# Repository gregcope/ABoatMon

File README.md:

ABoatMon
========

An Arduno clone based (hence the A) Boat Monitoring solution!

Intro
=====

A reimplementation, and extension of https://github.com/gregcope/piboatmon, as the original consumed too much power.  This is designed with the following goals;
* Be very, very low power and
* Monitor and charge from 12-24V

The present version is made from COTS parts to make life easy at the deign/proto stage.  However the code should be transferable.

Parts
=====
* [Adafruit Ultimate GPS](https://www.adafruit.com/product/746) - any 3.3v UART GPS would do, however needs an enable pin and vbat GPS almanac backup
* [Adafruit Fona](https://www.adafruit.com/product/1946) - any 3.3v UART GSM modem would do, although we do use the battery charging on the fona
* [Low power Atemega 1280 Moteino Mega](https://lowpowerlab.com/shop/product/119) This might fit into lower spec Atmegs, but I have no idea... The [Moteino M0 would work well](https://lowpowerlab.com/shop/product/184), although pin outs need to change.
* [Mini Step Down Regulator Voltag Power Supply Module 4.5v~55v to 5v](https://www.ebay.co.uk/sch/i.html?_osacat=0&_odkw=Mini+Step+Down+Regulator+Voltag+Power+Supply+Module+4.5v~55v+to+5v&_from=R40&_trksid=p2334524.m570.l1313.TR0.TRC0.H0.XMini+Step+Down+Regulator+Voltag+Power+Supply+Module+4.5v~55v+to+5v+600ma.TRS0&_nkw=Mini+Step+Down+Regulator+Voltag+Power+Supply+Module+4.5v~55v+to+5v+600ma&_sacat=0).  Specifically the one with an enable pin and low power in off mode (<10ua).  Needs to supply 500ma+ (600ma is fine) and deal with 11-30v on the input to work on 12V or 24V systems.  Needs to supply 5V for the lipo charger.  Efficiency is not a massive issue as the regulator is off most of the time, only on to charge occassionally.
* [DS18B20 Waterproof Digital Probe Temperature Sensor with Silicone Cable (higher temp) Thermometer](https://www.ebay.co.uk/sch/i.html?_from=R40&_trksid=p2380057.m570.l1313.TR0.TRC0.H0.Xvermont+l+tent.TRS0&_nkw=DS18B20+Waterproof+Digital+Probe+Temperature+Sensor+Silicone+Cable+Thermometer&_sacat=0)
* [12V 12mm LED Power Push Button Switch Momentary Waterproof Metal 4 Pin](https://www.ebay.co.uk/sch/i.html?_osacat=0&_odkw=waterproof+LED+switch+12mm&_from=R40&_trksid=p2334524.m570.l1313.TR0.TRC0.H0.Xwaterproof+LED+switch+12mm+momentary.TRS0&_nkw=waterproof+LED+switch+12mm+momentary&_sacat=0)
* 1200mah LIPO Battery (any single cell LIPO with a JST would do)
* Bilge Switch (any normally closed, simple switch would do)

External Libs
=======

* [Tinygps++](https://github.com/mikalhart/TinyGPSPlus) - A class to deal with GPS
* [Lowpower](https://github.com/LowPowerLab/LowPower) - A class to help with Sleep modes
* Eeprom - Save Eeprom state
* [OneWire](https://github.com/PaulStoffregen/OneWire) - DS18B20 Temp sensor lib

Internal Classes
========
* Config - A class to provide a config object to store Eeprom state
* CRC8 - CRC checksum (for config saving)
* Sleep - Simple wrapper to LowPower sleep
* Buton - A simple button monitor
* Fona - Drive a fona to send data
* Gps - Drive a GPS and feed a TinyGPS++ object with other helper methods
* Led - A simple LED driver
* Lipo - A class to ADC a Lipo value
* Temp - A class with simple, non-sleeping temp measurements
* Vcc - A class to ADC the VCC, as well as enable/disable a regulartor (that drives the 5v Lipo charger)

High Level Logic
================

* Switches is on setup configures all the required parts
* Loop every 8 secs and checks;
   * Start the temp conversion 
   * Lipo volts
   * VCC (and enable regulator if Vcc > 13 and switch off if low)
   * Bilge switch
   * read temp (blocks)
* Every Hour;
   * Checks the above
   * Checks location
* If out of band, send a message as an alarm
* Daily
   * Send a message

VCC logic - Sacrifical Charging
================
The idea is that if VCC is 13v plus then a charge source is on and we can hence enable the regulator.  If the VCC is above REG_ON_VOLTS (13v) enable the regulator to start the LIPO charger.  If below REG_OFF_VOLTS (12.8) stop regulator

Message Sending
================
To save possible expensive bandwidth the message is compressed.  Ideally it would be JSON.  However it is optimised for speed and bandwidth costs.  It needs to be parsed on arrival.

HowTo
=====

1. Open a command terminal, and change cd to where your Ardunio IDE stores code
```cd Documents/Arduino```
2. Clone the repo
```git clone https://github.com/gregcope/ABoatMon.git```
3. Open Ardunio IDE and open ```ABoatMon.ino```

http://arduino.stackexchange.com/questions/348/how-to-organize-my-arduino-projects-structure-for-easy-source-control

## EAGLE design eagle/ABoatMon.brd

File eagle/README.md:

# Eagle Files

0. Uses Sparkfun DRC file
1. ERC and DRC check clean!
2. Bottom Copper Pour
3. Nets Classes use 24mil width and 16mil clearance
4. Polygons use Isolate 12mil
5. Layer 26 bNames - bottom silkscreen has board dimensions on it

## Design

0. I may add more parts...
1. Uses a MoteinoMega, Adafruit Ultimate GPS and an Adafruit FONA GSM
2. The P-channel Mosfet is designed to power the GPS directly, avoiding the on board regulator
3. The VBAT is on the MotinoMega 3.3V rail to keep the GPS backup circuits powered
4. The JST is for a Lipo battery
5. Their is a 1.8M/3.3M VCC voltage divider to monitor the LIPO, with a 0.1uF capacitor - see [Jeelabs post here](https://jeelabs.org/2013/05/16/measuring-the-battery-without-draining-it/)
6. Terminal Connector is for a simple Bilge switch for the Moteino to monitor
7. Terminal Connector for a Button
8. Terminal Connector for an LED
9. Terminal Connector for a DS18B20 Temp probe powered from a GPIO pin
10. Terminal Connector 12V-24V VCC input
11. A 27M/3.3M voltage divider to measure 30+V on an ADC pin
12. Headers for Fona GSM module
13. Terminal Connector for a 5v cable to connect to the Fona USB charge port
14. There is a jumper to measure the uCurrent the board uses from the LIPO, and also by-pass the switching (aka an on/off switch)
15. There is a jumper to measure the uCurrent the board uses from VCC, and also by-pass the switching (aka an on/off switch)
16. Voltage regulator uses a [holtek HT7463A](http://www.holtek.com/documents/10179/116711/HT7463A_Bv130.pdf)

... What's missing?

No thread is complete without pictures...

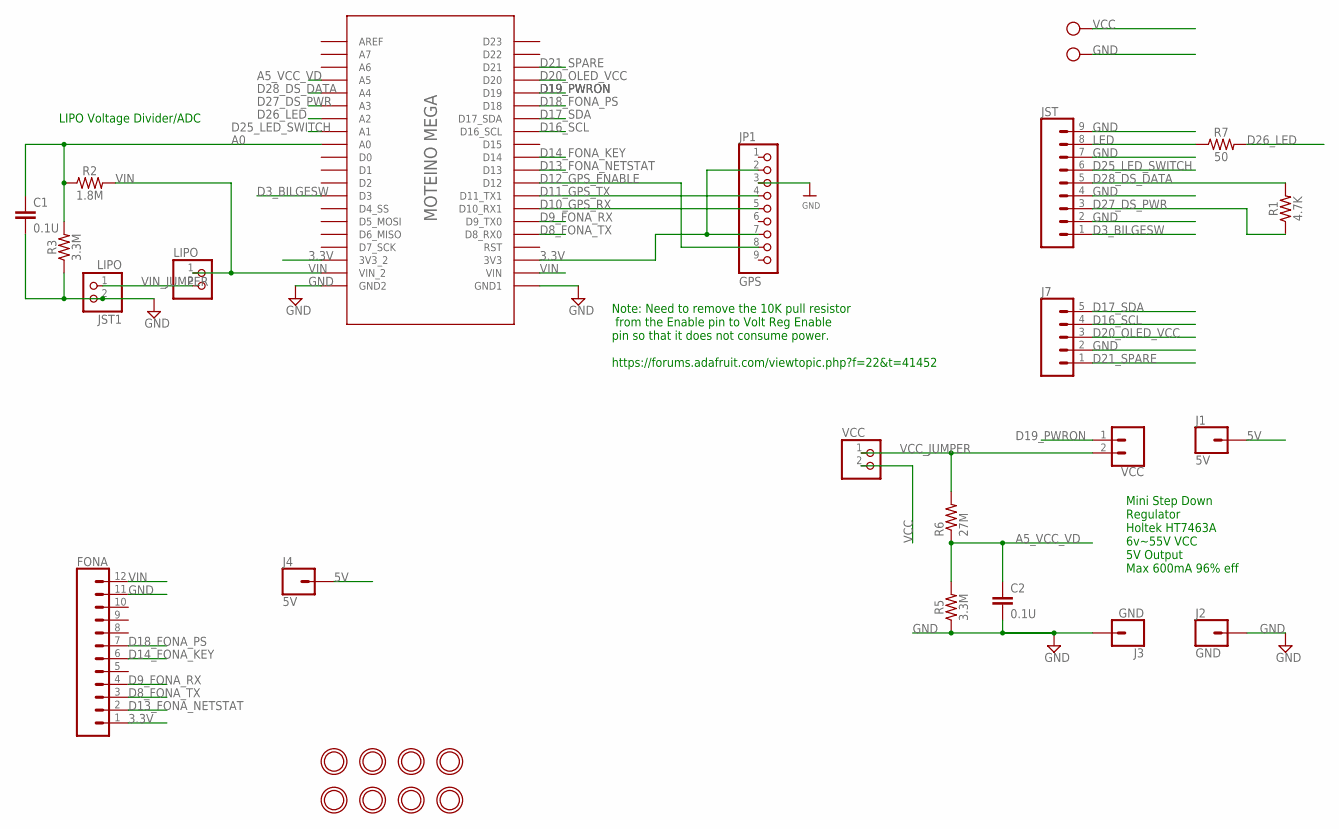
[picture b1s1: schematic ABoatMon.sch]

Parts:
C1, C2: 0.1U; CAP-PTH-SMALL-KIT
ENABLE: VCC; 1X02
FONA: CONN_12; 1X12
GND: MOUNTINGHOLE2.5; MOUNTINGHOLE_2.5_PLATED
J1, J4: 5V; 1X01
J2, J3: GND; 1X01
J7: CONN_05NO_SILK; 1X05_NO_SILK
JP1: GPS; 1X09_ROUND_70
JST: CONN_09; 1X09
JST1: LIPO; JST-PH-2-THM
LIPO: HEADER-1X2ROUND; 1X02_ROUND
MOTEINO_MEGA: HEADERS; MOTEINO_MEGA_SIMPLE
R1: 4.7K; AXIAL-0.3
R2: 1.8M; AXIAL-0.3
R3, R5: 3.3M; AXIAL-0.3
R6: 27M; 0309/12
R7: 50; AXIAL-0.3
U$1, U$2, U$3, U$4, U$5, U$7, U$8: MOUNTINGHOLE2.5; MOUNTINGHOLE_2.5_PLATED
VCC: HEADER-1X2ROUND; 1X02_ROUND
X1: MKDSN1,5/2-5,08

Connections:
3.3V: FONA.1, JP1.2, JP1.7, MOTEINO_MEGA.3V3, MOTEINO_MEGA.3V3_2
5V: J1.1, J4.1
A0: C1.1, MOTEINO_MEGA.A0, R2.P$1 (1), R3.P$2 (2)
A5_VCC_VD: C2.1, MOTEINO_MEGA.A5, R5.P$2 (2), R6.1
D3_BILGESW: JST.1, MOTEINO_MEGA.D3
D8_FONA_TX: FONA.3, MOTEINO_MEGA.D8 (D8_RX0)
D9_FONA_RX: FONA.4, MOTEINO_MEGA.D9 (D9_TX0)
D10_GPS_RX: JP1.5, MOTEINO_MEGA.D10 (D10_RX1)
D11_GPS_TX: JP1.4, MOTEINO_MEGA.D11 (D11_TX1)
D12_GPS_ENABLE: JP1.8, MOTEINO_MEGA.D12
D13_FONA_NETSTAT: FONA.2, MOTEINO_MEGA.D13
D14_FONA_KEY: FONA.6, MOTEINO_MEGA.D14
D16_SCL: J7.4, MOTEINO_MEGA.D16 (D16_SCL)
D17_SDA: J7.5, MOTEINO_MEGA.D17 (D17_SDA)
D18_FONA_PS: FONA.7, MOTEINO_MEGA.D18
D19_PWRON: ENABLE.1, MOTEINO_MEGA.D19
D20_OLED_VCC: J7.3, MOTEINO_MEGA.D20
D21_SPARE: J7.1, MOTEINO_MEGA.D21
D25_LED_SWITCH: JST.6, MOTEINO_MEGA.A1
D26_LED: MOTEINO_MEGA.A2, R7.P$2 (2)
D27_DS_PWR: JST.3, MOTEINO_MEGA.A3, R1.P$1 (1)
D28_DS_DATA: JST.5, MOTEINO_MEGA.A4, R1.P$2 (2)
GND: C1.2, C2.2, FONA.11, J2.1, J3.1, J7.2, JP1.3, JST.2, JST.4, JST.7, JST.9, JST1.2 (1), MOTEINO_MEGA.GND1, MOTEINO_MEGA.GND_2 (GND2), R3.P$1 (1), R5.P$1 (1), X1.2
LED: JST.8, R7.P$1 (1)
VCC: VCC.2, X1.1
VCC_JUMPER: ENABLE.2, R6.2, VCC.1
VIN: FONA.12, LIPO.1, MOTEINO_MEGA.VIN, MOTEINO_MEGA.VIN_2, R2.P$2 (2)
VIN_JUMPER: JST1.1 (2), LIPO.2

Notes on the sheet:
LIPO Voltage Divider/ADC
Mini Step Down Regulator Holtek HT7463A 6v~55V VCC 5V Output Max 600mA 96% eff
Note: Need to remove the 10K pull resistor from the Enable pin to Volt Reg Enable pin so that it does not consume power. https://forums.adafruit.com/viewtopic.php?f=22&t=41452

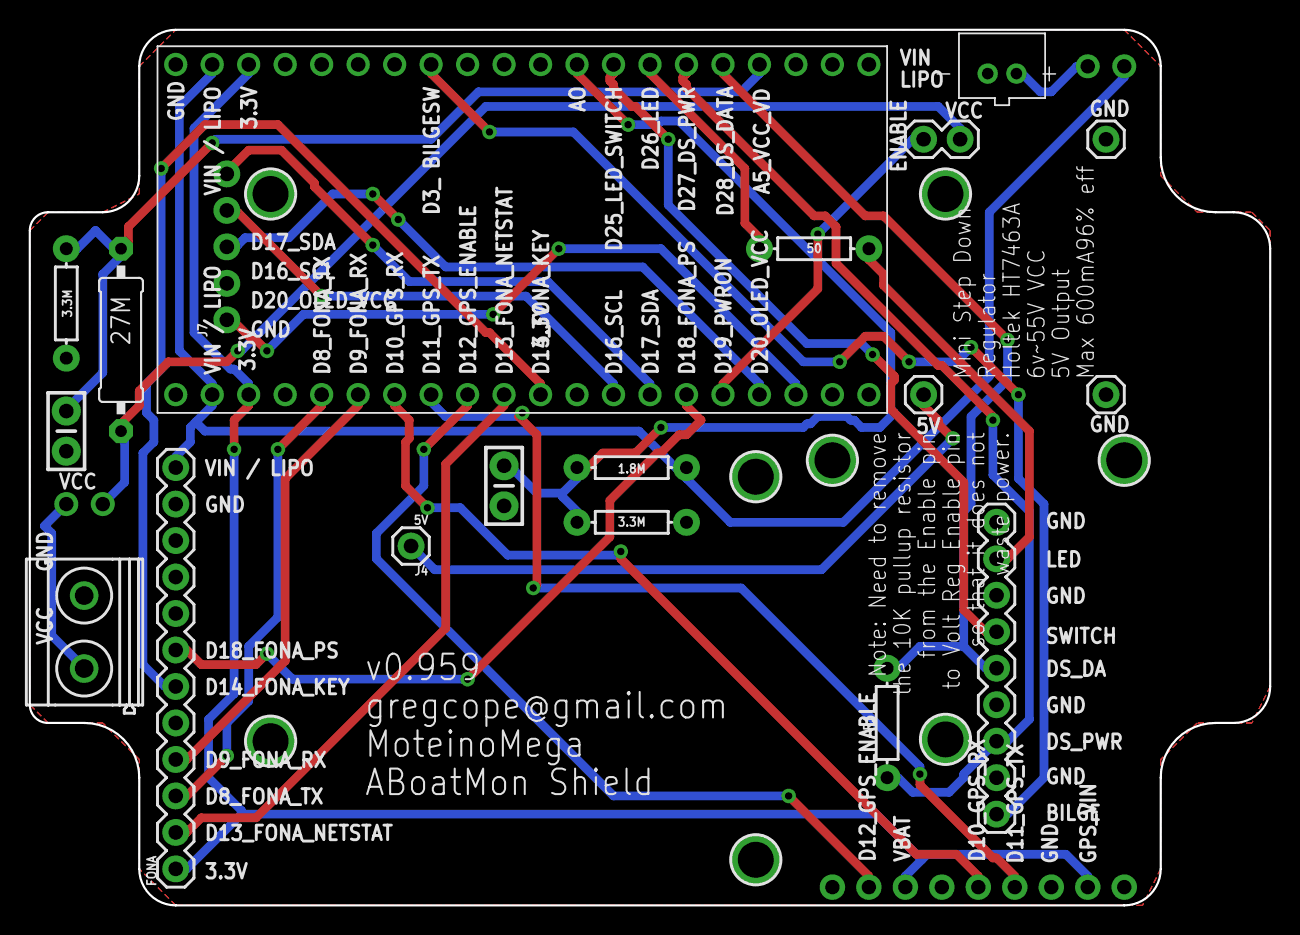
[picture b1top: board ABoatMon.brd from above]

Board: 2 copper layers, 86.4 x 61.0 mm, 30 parts (0 on the bottom side), 28 nets.

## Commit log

2016-05-03 Inital commit
2016-05-03 Added gitignore
2016-05-03 Change file names
2016-05-03 Added Device Class
2016-05-03 Added Device Class to README
2016-05-03 Ops forgot this one\!
2016-05-03 Doco update
2016-05-03 Added LED, ChargerPin and GPS setup
2016-05-03 Adding keywords
2016-05-04 Started GPS setup config logic
2016-06-01 Update including files
2016-06-01 Comments / doco update
2016-06-01 Added start method to Device
2016-06-11 Changed GPS Power Pin
2016-06-11 Added LED switch and Bilge Switch logic
2016-06-11 Refined and tested bilge Switch logic and added message logic
2016-06-11 tweaks to check/message logic
2016-06-11 trying to sort battery monitoring
2016-06-12 Finally got the VoltDivider working, and string concat\!
2016-06-12 Capture any changes I forgot...
2016-06-15 Started Temp monitoring
2016-06-15 Changed name to lipoBatt...
2016-06-15 Changed name to lipoBatt... and a few I missed
2016-07-01 Lots of changes, inc GPS fix timeout
2016-07-02 Inital Config Class
2016-07-02 Added CRC8 libs
2016-07-02 Start of a Config class
2016-07-02 README update
2016-07-03 Lots of changes, but working Config object
2016-07-03 GPS tweaks
2016-07-03 Moved sleep functions to object
2016-07-03 Added checksum to save and load
2016-07-03 Started sorted GPS setup, startup
2017-03-04 Notes
2017-04-14 Lots of changes.... sorry
2017-04-14 Added logic to check for fix
2017-04-14 changed to ISO time, HDOP tweaks
2017-05-01 Wrap up. BilgeSwtich working
2017-05-07 Voltage divider working, GPS on P-Mosfet
2017-06-18 General catchup... sorry
2017-09-23 added v0.1 eagle files
2017-09-23 Adding PDFs
2017-09-24 Adding Sparkfun standard DRU
2017-09-24 V0.2 No errors, Bottom layer copper pour
2017-09-24 Readme
2017-09-24 Readme .. typo
2017-09-24 Design ideas, links
2017-09-24 v0.3 ... GSM plus right Mega headers
2017-09-24 v0.3 ... update PDFs and PNGs
2017-09-25 Adding oshpark DRU
2017-09-25 Removing PDFs
2017-09-25 fixes....
2017-09-26 Added v0.61
2017-09-30 V0.91. Changed netclasses, autorouted, tidied names. Bar one Width and a few angle errors passes sparkfun and oshpark DRC rules
2017-09-30 V0.97 - Silkscreen fixes
2017-10-01 V0.98, schematic layout tweaks, corrected GSM power error, removed GSM power
2017-10-01 Added reverse polarity protection and fuse, as well as GSM FET
2017-10-02 Moved things around, changed P-fets
2017-10-07 Changed Resistor shapes
2017-10-08 Added current limiting resistors
2017-10-13 Routed 100%, finally
2017-10-13 tNames changes
2017-10-21 Changed pins to reflect actual design
2017-10-21 DS wiring
2018-05-19 Sweep up
2018-05-19 eagle updates
2018-06-09 New eagle files
2018-06-15 Added parts
2018-06-15 Another go...
2018-07-04 new .gitignore
2018-07-08 v 2.99
2018-07-09 simplified to use GPS enable pin, reduce BOM. Need to remove 10K pull-up on Enable pin
2018-07-09 doco added
2018-07-09 rollback
2018-07-09 Smaller layout, swapped gps
2018-07-24 Silkscreen updates
2018-07-24 Silkscreen updates+routing
2018-10-28 v2.99 - complete relayout
2018-10-28 v2.99 gerbers sent to JLCPCB
2018-10-28 Added the other 3v rail, silkscreen fixes
2018-10-28 Doco update II
2018-10-28 Doco update III
2018-10-28 removing images
2018-10-28 Adding images
2018-10-28 README change
2018-10-28 Added header info
2018-10-28 Added screw term info
2018-10-28 email addy change
2018-10-29 more design info
2018-11-03 LIPO jumper correction. Reroute+better ground pours
2018-11-03 new images
2018-11-03 Doh. fona swapped round, VCC header fix, better GND pour
2018-11-03 fixed a DRC issue
2018-11-04 updated gitignore
2018-11-04 Addig sonoff case datasheet
2018-11-09 v0.649 - rotate gps, fona, move TH parts, remove 5v and GND screw
2018-11-11 v0.649 - moved screw terminal headers
2018-11-17 Silkscreen improvements
2018-11-17 Silkscreen improvements II
2018-11-17 Silkscreen typo
2018-11-17 lots of gnd vias
2018-11-21 Silkscreen fixes for D18, D19
2018-11-23 Silkscreen fixes for D18, D19 II
2018-11-23 changed layout for sonoff box
2018-11-23 removing old board
2018-11-24 trueup
2018-12-08 Moved boxmounting holes 3mm
2018-12-09 starting again
2018-12-09 refactor
2018-12-17 bigger JST, added 4.7K
2018-12-17 DRC, ERC pass
2018-12-17 updated images
2018-12-18 Setup GPS and lipo code
2018-12-20 Updated libs in README
2018-12-20 Fixed gps fix code ...
2018-12-20 lipo code vaguly working
2018-12-20 updated lipo code
2018-12-23 sleep/resume works. Fix borked - need to update gps/nmea object before reusing it
2018-12-23 sorta fixed gps update
2018-12-25 sorta fixed gps update part deux
2019-01-02 changed size of endy bit
2019-01-02 rerouting to add more vias
2019-01-03 removed extra 3.3v labels
2019-01-05 Slikscreenfixes, code into debug mode
2019-01-05 png updates
2019-01-05 another png update ..
2019-01-06 Adding vcc files, gps optimisations
2019-01-06 Updated vcc class
2019-01-09 GPS fix tweaks
2019-01-09 Initial commit of Fona class
2019-01-12 Initial commit of LED, and GPS fixes
2019-01-13 Added Mote LED, GPS optimsations
2019-01-13 first commit of temp, and start of checks logic
2019-01-18 moved 9 pin jst
2019-01-19 temp code
2019-01-20 Temp refactor ... old version does not work ...
2019-01-20 Temp refactor ... works, too much code
2019-01-21 Negative works, plus temp alarms
2019-01-22 Button class, remove Device
2019-01-22 Comments update for Led.cpp
2019-01-22 Check logic
2019-01-22 keyword update
2019-01-23 vcc logic
2019-01-24 Button comments
2019-01-24 Comments update
2019-01-26 Button fixpwdpwd
2019-01-26 Vcc fixes
2019-01-26 moved large JST
2019-01-27 message vars
2019-01-27 getdateTime
2019-01-27 logic to only update datetime if old
2019-01-27 send message logic
2019-01-28 LITERAL1
2019-02-02 Refactor send messages
2019-02-02 logic change
2019-02-02 message and location logic
2019-02-02 message logic
2019-02-03 eagle jst added
2019-02-03 added JST - drc issues still
2019-02-03 v0.899 board design - irgnoring DRC checks
2019-02-03 Removed some debug command, started messageStr
2019-02-03 added _time method
2019-02-03 added logic and add missing line
2019-02-03 typo, comment added
2019-02-03 Added getLat getLon and keywords update
2019-02-03 Gps distance moved, message improvements, testing commit
2019-02-03 Message dateTime working
2019-02-03 lat, lon debug
2019-02-03 distance debug
2019-02-03 distance debug and lon wrong...
2019-02-05 fix latlon
2019-02-05 Removed debug, tidy
2019-02-06 changed to pass by referance to save code and vars
2019-02-09 fixed vcc
2019-02-10 removed debug messages - tidy
2019-02-11 starting fona code
2019-02-12 apn settings
2019-02-13 Improved lipo formula
2019-02-13 Improved lipo formula removed debug
2019-02-13 rename Fona wrapper class to Modem
2019-02-14 adding files
2019-02-23 Started NeoGPS POC
2019-02-23 Gns on, off, init, powerStat
2019-02-23 Added custom GPSport.h
2019-02-23 Configure NMEAGPS_cfg.h GPSfix_cfg.h
2019-02-24 much faffing
2019-03-04 Lots of small updates
2019-03-04 Lots of small updates II
2019-03-23 0.949
2019-03-23 latest board
2019-03-29 More GPS notes
2019-04-01 Moving to integer/long maths for lat, lon
2019-04-05 v0.959 board layout, moved to 0.1 not jst
2019-05-05 Remove NeoGPS
2019-05-05 Remove GNS class

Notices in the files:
parts and their libraries:
SparkFun-Capacitors: Licensing: Creative Commons ShareAlike 4.0 International - https://creativecommons.org/licenses/by-sa/4.0
